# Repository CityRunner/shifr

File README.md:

# Shifr Keyboard

Shifr (ШИФР) is a compact wireless mechanical keyboard featuring only 40 switches.

The exclusive use of through-hole components simplifies assembly and contributes to its rugged DIY aesthetic.

# Images
| Front                                      | Back                                      |
|--------------------------------------------|-------------------------------------------|
|  |  |

# Layout
Default layout is Colemak-DH with homerow mods.

# Building

## Bill of materials
| Value | Designator | Footprint | Quantity |
|---|---|---|---|
| Battery | BT1 | JST_PH_S2B-PH-K_1x02_P2.00mm_Horizontal | 1 |
| Diode | D1 - D40 | Diode_DO-35 | 40 |
| Keyswitch | S1 - S40 | MX_PCB_1.00u | 40 |
| Power Switch | SW1 | SW_CuK_OS102011MA1QN1_SPDT_Angled | 1 |
| Reset Switch | SW2 | SW_TH_Tactile_Omron_B3F-10xx | 1 |
| Nice_Nano_V2 | U1 | Nice_Nano_V2 | 1 |
| Cherry MX Keycaps | - | - | 40 |
| 3.7V LiPo Battery | - | - | 1 |
| M2 Screws with Nuts | - | - | 5 |
| 3mm Spacers | - | - | 5 |

## Firmware
1. Download and unpack [misc/](https://github.com/CityRunner/shifr/tree/main/misc)firmware.zip.
2. Double-tap the Reset button on the keyboard.
3. Copy "shifr-nice_nano_v2-zmk.uf2" onto the root directory of the USB storage that appears.
4. The controller should flash the firmware and automatically restart once flashing is complete.

Source code available here: [Shifr ZMK](https://github.com/CityRunner/shifr-zmk)

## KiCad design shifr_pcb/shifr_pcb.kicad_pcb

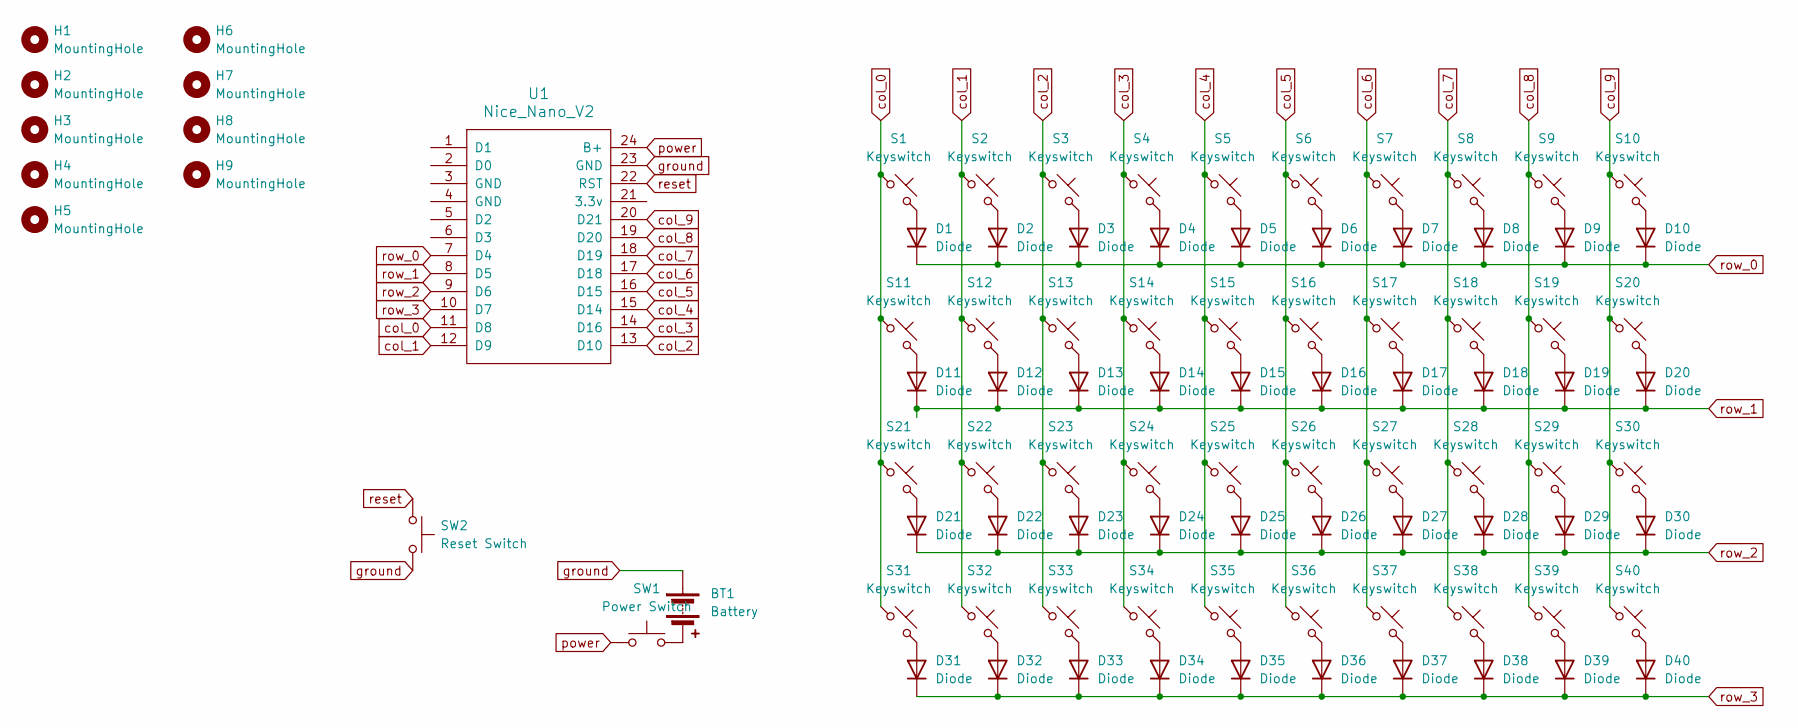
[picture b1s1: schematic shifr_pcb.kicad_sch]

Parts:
BT1: Battery; JST_PH_S2B-PH-K_1x02_P2.00mm_Horizontal
D1, D2, D3, D4, D5, D6, D7, D8, D9, D10, D11, D12, D13, D14, D15, D16, D17, D18, D19, D20, D21, D22, D23, D24, D25, D26, D27, D28, D29, D30, D31, D32, D33, D34, D35, D36, D37, D38, D39, D40: Diode; Diode_DO-35
H1, H2, H3, H4, H5: MountingHole; MountingHole_2.2mm_M2_Pad_Via
H6, H7, H8, H9: MountingHole; MountingHole_2.2mm_M2_ISO14580
S1, S2, S3, S4, S5, S6, S7, S8, S9, S10, S11, S12, S13, S14, S15, S16, S17, S18, S19, S20, S21, S22, S23, S24, S25, S26, S27, S28, S29, S30, S31, S32, S33, S34, S35, S36, S37, S38, S39, S40: Keyswitch; MX_PCB_1.00u
SW1: Power Switch; SW_CuK_OS102011MA1QN1_SPDT_Angled
SW2: Reset Switch; SW_TH_Tactile_Omron_B3F-10xx
U1: Nice_Nano_V2

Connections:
unnamed: BT1.2 (-), SW1.2
unnamed: D1.2 (A), S1.2
unnamed: D2.2 (A), S2.2
unnamed: D3.2 (A), S3.2
unnamed: D4.2 (A), S4.2
unnamed: D5.2 (A), S5.2
unnamed: D6.2 (A), S6.2
unnamed: D7.2 (A), S7.2
unnamed: D8.2 (A), S8.2
unnamed: D9.2 (A), S9.2
unnamed: D10.2 (A), S10.2
unnamed: D11.2 (A), S11.2
unnamed: D12.2 (A), S12.2
unnamed: D13.2 (A), S13.2
unnamed: D14.2 (A), S14.2
unnamed: D15.2 (A), S15.2
unnamed: D16.2 (A), S16.2
unnamed: D17.2 (A), S17.2
unnamed: D18.2 (A), S18.2
unnamed: D19.2 (A), S19.2
unnamed: D20.2 (A), S20.2
unnamed: D21.2 (A), S21.2
unnamed: D22.2 (A), S22.2
unnamed: D23.2 (A), S23.2
unnamed: D24.2 (A), S24.2
unnamed: D25.2 (A), S25.2
unnamed: D26.2 (A), S26.2
unnamed: D27.2 (A), S27.2
unnamed: D28.2 (A), S28.2
unnamed: D29.2 (A), S29.2
unnamed: D30.2 (A), S30.2
unnamed: D31.2 (A), S31.2
unnamed: D32.2 (A), S32.2
unnamed: D33.2 (A), S33.2
unnamed: D34.2 (A), S34.2
unnamed: D35.2 (A), S35.2
unnamed: D36.2 (A), S36.2
unnamed: D37.2 (A), S37.2
unnamed: D38.2 (A), S38.2
unnamed: D39.2 (A), S39.2
unnamed: D40.2 (A), S40.2
col_0: S1.1, S11.1, S21.1, S31.1, U1.11 (D8)
col_1: S2.1, S12.1, S22.1, S32.1, U1.12 (D9)
col_2: S3.1, S13.1, S23.1, S33.1, U1.13 (D10)
col_3: S4.1, S14.1, S24.1, S34.1, U1.14 (D16)
col_4: S5.1, S15.1, S25.1, S35.1, U1.15 (D14)
col_5: S6.1, S16.1, S26.1, S36.1, U1.16 (D15)
col_6: S7.1, S17.1, S27.1, S37.1, U1.17 (D18)
col_7: S8.1, S18.1, S28.1, S38.1, U1.18 (D19)
col_8: S9.1, S19.1, S29.1, S39.1, U1.19 (D20)
col_9: S10.1, S20.1, S30.1, S40.1, U1.20 (D21)
ground: BT1.1 (+), SW2.2, U1.23 (GND)
power: SW1.1, U1.24 (B+)
reset: SW2.1, U1.22 (RST)
row_0: D1.1 (K), D2.1 (K), D3.1 (K), D4.1 (K), D5.1 (K), D6.1 (K), D7.1 (K), D8.1 (K), D9.1 (K), D10.1 (K), U1.7 (D4)
row_1: D11.1 (K), D12.1 (K), D13.1 (K), D14.1 (K), D15.1 (K), D16.1 (K), D17.1 (K), D18.1 (K), D19.1 (K), D20.1 (K), U1.8 (D5)
row_2: D21.1 (K), D22.1 (K), D23.1 (K), D24.1 (K), D25.1 (K), D26.1 (K), D27.1 (K), D28.1 (K), D29.1 (K), D30.1 (K), U1.9 (D6)
row_3: D31.1 (K), D32.1 (K), D33.1 (K), D34.1 (K), D35.1 (K), D36.1 (K), D37.1 (K), D38.1 (K), D39.1 (K), D40.1 (K), U1.10 (D7)

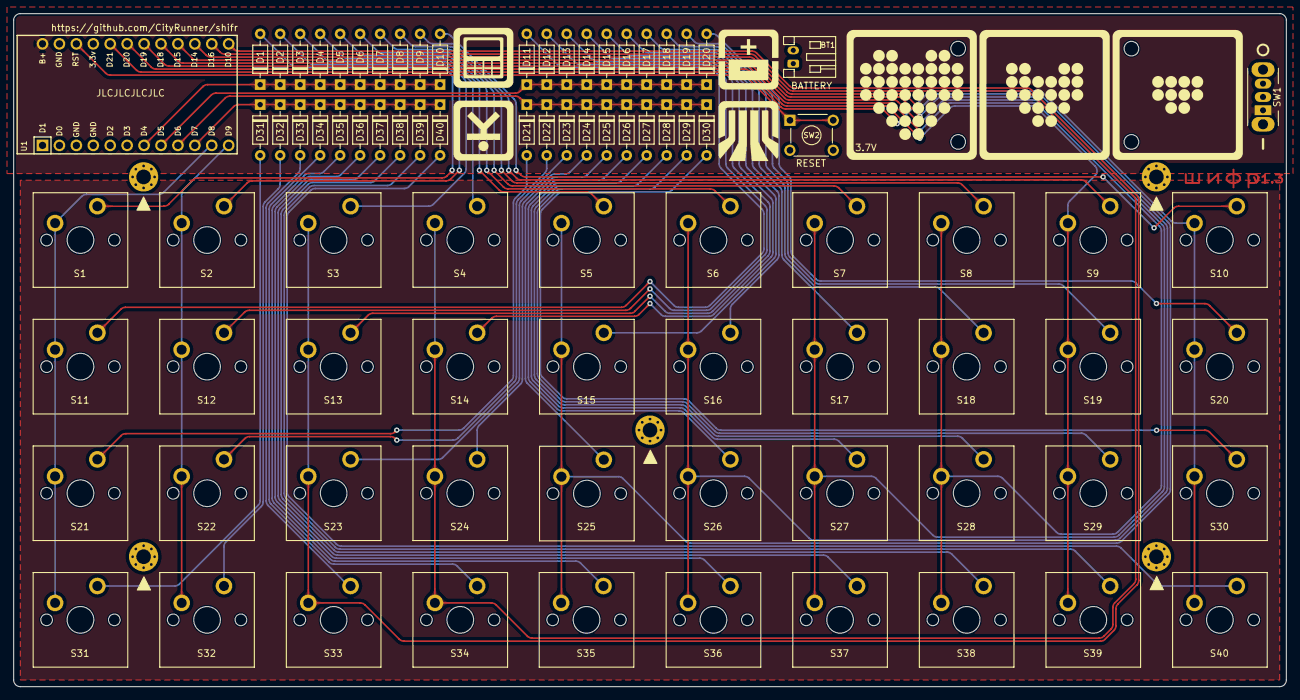
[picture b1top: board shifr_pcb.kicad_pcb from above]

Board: 2 copper layers, 191.0 x 101.0 mm, 93 parts (0 on the bottom side), 58 nets.

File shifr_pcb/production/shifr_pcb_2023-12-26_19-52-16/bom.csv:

Designator,Footprint,Quantity,Value,LCSC Part #
BT1,JST_PH_S2B-PH-K_1x02_P2.00mm_Horizontal,1,Battery,
"D1, D10, D11, D12, D13, D14, D15, D16, D17, D18, D19, D2, D20, D21, D22, D23, D24, D25, D26, D27, D28, D29, D3, D30, D31, D32, D33, D34, D35, D36, D37, D38, D39, D4, D40, D5, D6, D7, D8, D9",Diode_DO-35,40,Diode,
"H1, H2, H3, H4, H5",MountingHole_2.2mm_M2_Pad_Via,5,MountingHole,
"H6, H7, H8, H9",MountingHole_2.2mm_M2_ISO14580,4,MountingHole,
"S1, S10, S11, S12, S13, S14, S15, S16, S17, S18, S19, S2, S20, S21, S22, S23, S24, S25, S26, S27, S28, S29, S3, S30, S31, S32, S33, S34, S35, S36, S37, S38, S39, S4, S40, S5, S6, S7, S8, S9",MX_PCB_1.00u,40,Keyswitch,
SW1,SW_CuK_OS102011MA1QN1_SPDT_Angled,1,Power Switch,
SW2,SW_TH_Tactile_Omron_B3F-10xx,1,Reset Switch,
U1,Nice_Nano_V2,1,Nice_Nano_V2,

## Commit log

2024-01-19 Upload project files
2024-01-21 Replace schematic image with pdf
2024-01-21 Remove production files
2024-03-19 Add firmware.zip and layout.png
